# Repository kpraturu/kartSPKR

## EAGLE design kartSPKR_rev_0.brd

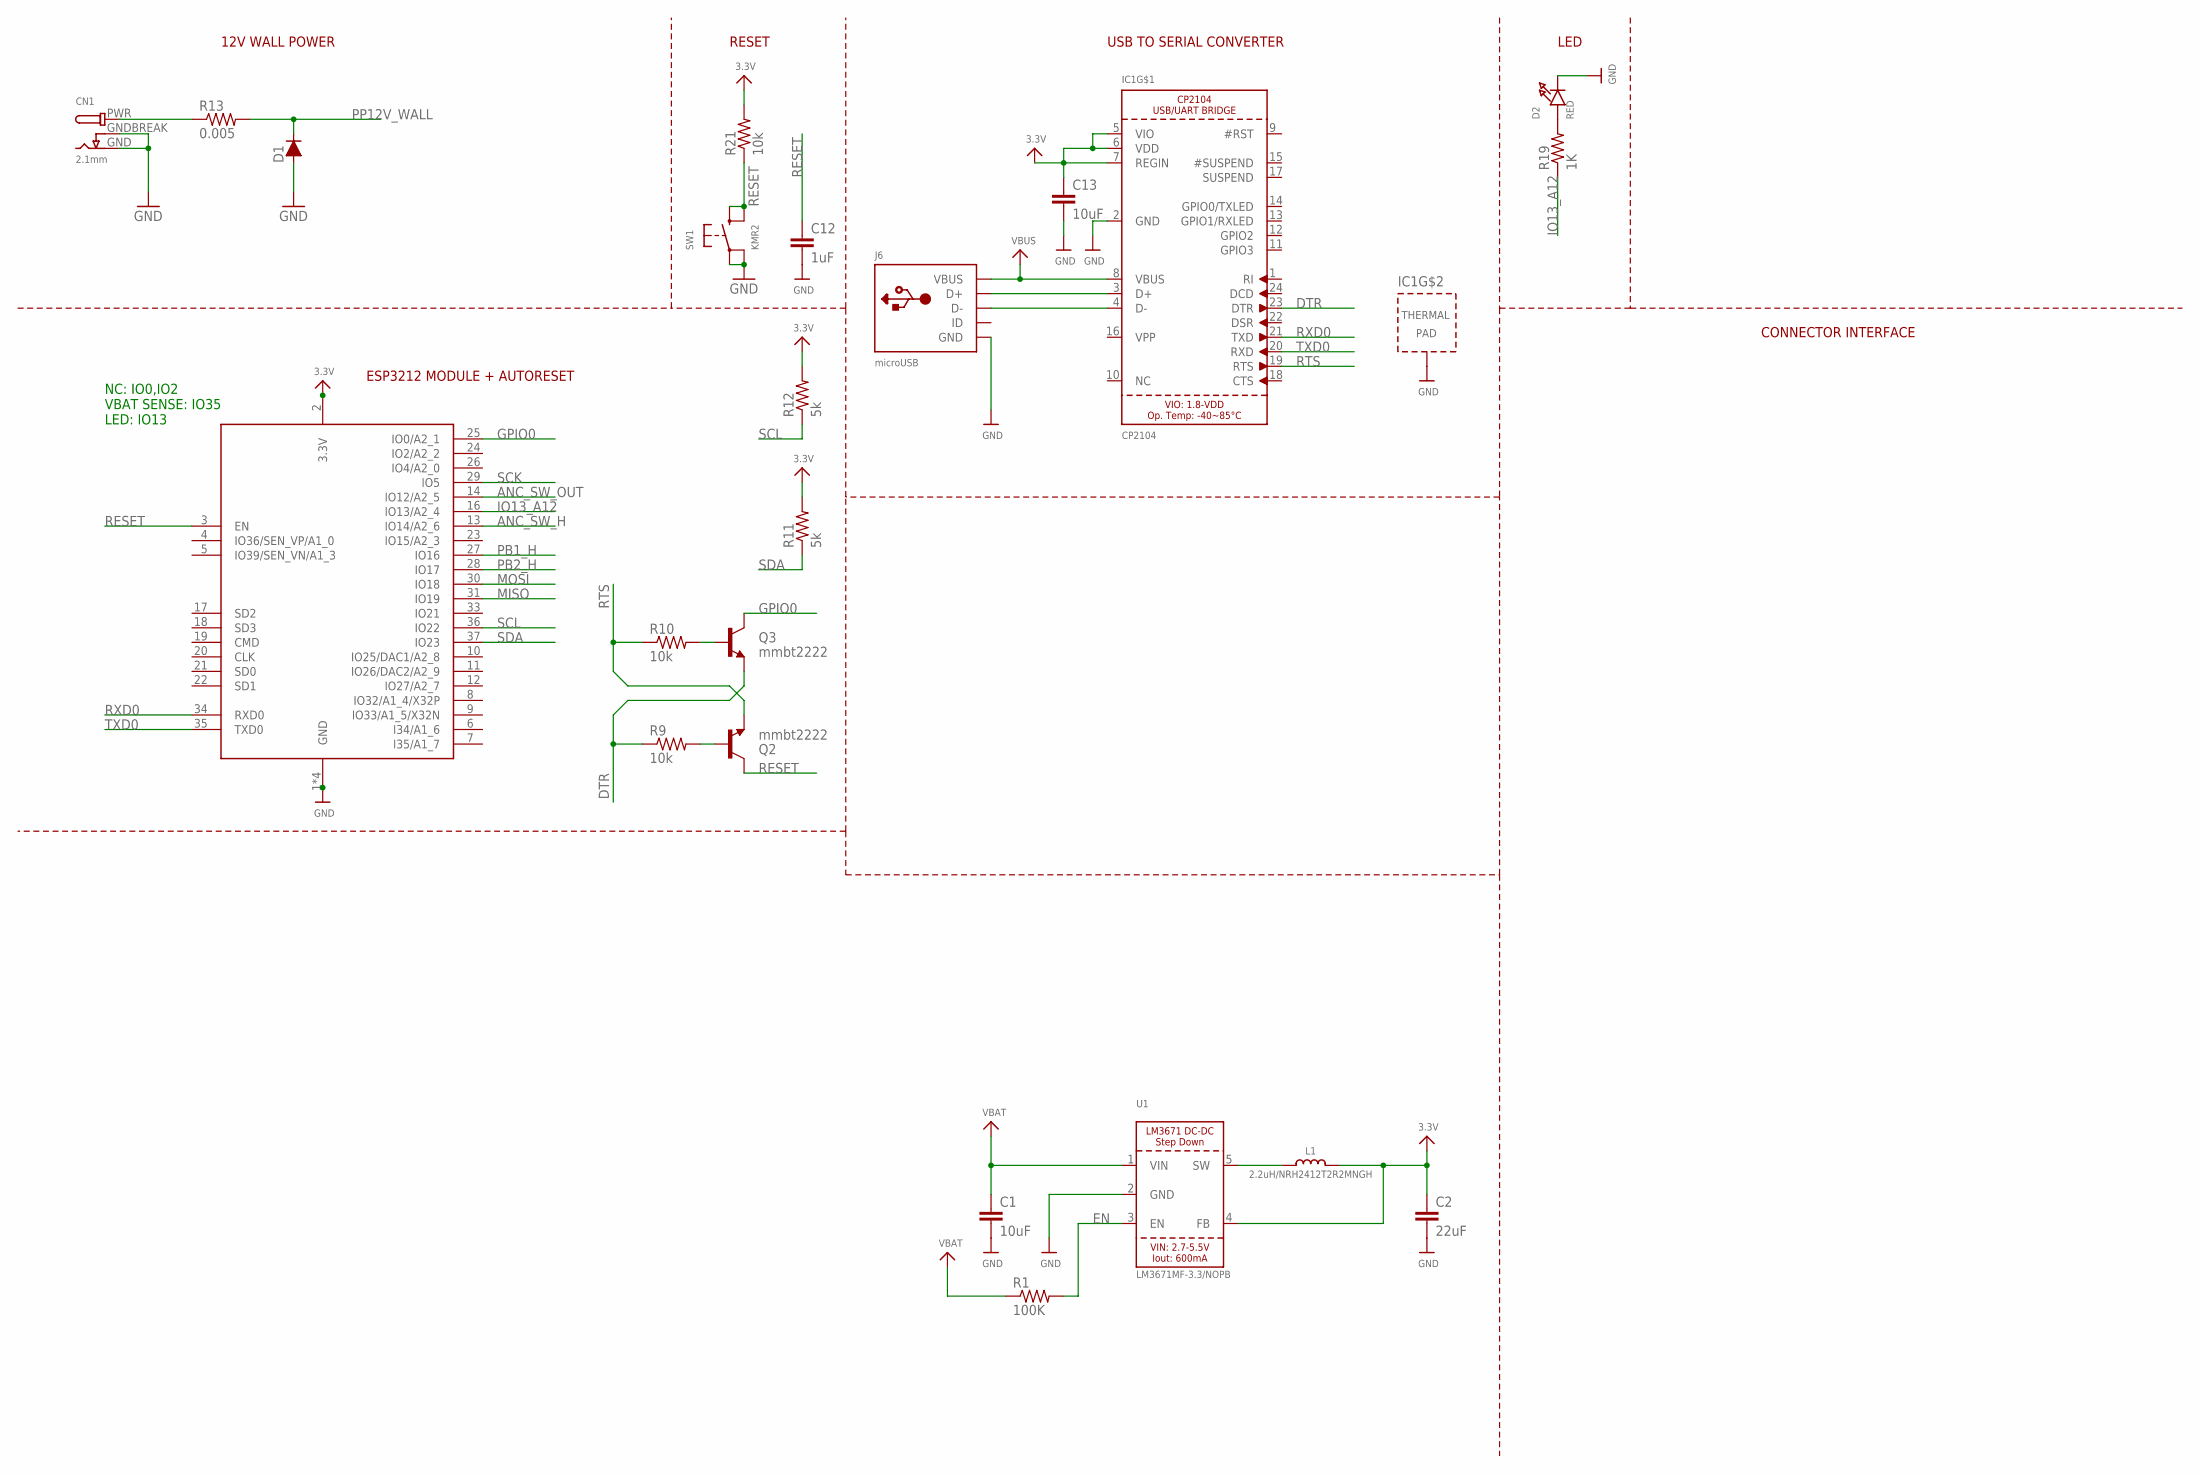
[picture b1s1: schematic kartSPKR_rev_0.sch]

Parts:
C1, C13: 10uF; C0603
C2: 22uF; C0603
C12: 1uF; C0603
CN1: 2.1mm; DCJACK_2MM_SMT
D1: D-FILL-SMB; SMB
D2: RED; CHIPLED_0805_NOOUTLINE
IC1: CP2104; QFN24_4MM_SMSC
J6: microUSB; 4UCONN_20329
L1: 2.2uH/NRH2412T2R2MNGH; INDUCTOR_TAIYOYUDEN_NRH2412T
Q2, Q3: mmbt2222; SOT23-3
R1: 100K; R0603
R9, R10, R21: 10k; R0603
R11, R12: 5k; R0603
R13: 0.005; R1206
R19: 1K; R0603
SW1: KMR2; BTN_KMR2_4.6X2.8
U1: LM3671MF-3.3/NOPB; SOT23-5
X1: ESP32_WROOM32_SKINNY; WROOM32_SKINNY

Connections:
3.3V: C2.1, C13.1, IC1.5 (VIO), IC1.6 (VDD), IC1.7 (REGIN), L1.2, R11.2, R12.2, R21.2, U1.4 (FB), X1.2 (3.3V)
ANC_SW_H: X1.13 (IO14/A2_6)
ANC_SW_OUT: X1.14 (IO12/A2_5)
DTR: IC1.23 (DTR), Q3.2 (E), R9.1
EN: R1.2, U1.3 (EN)
GND: C1.2, C2.2, C12.2, C13.2, CN1.GND, CN1.GNDBREAK, D1.2 (A), D2.C, IC1.2 (GND), IC1.THERM (TP), J6.BASE@1 (GND), J6.BASE@2 (GND), J6.GND, J6.SPRT@1 (GND), J6.SPRT@2 (GND), J6.SPRT@3 (GND), J6.SPRT@4 (GND), SW1.A, SW1.A' (P1), U1.2 (GND), X1.1 (GND), X1.15 (GND), X1.38 (GND), X1.P$1 (GND)
GPIO0: Q3.3 (C), X1.25 (IO0/A2_1)
IO13_A12: R19.1, X1.16 (IO13/A2_4)
MISO: X1.31 (IO19)
MOSI: X1.30 (IO18)
unnamed: CN1.PWR, R13.1
unnamed: IC1.3 (D+), J6.D+
unnamed: D2.A, R19.2
unnamed: IC1.4 (D-), J6.D-
unnamed: Q2.1 (B), R9.2
unnamed: Q3.1 (B), R10.2
unnamed: L1.1, U1.5 (SW)
PB1_H: X1.27 (IO16)
PB2_H: X1.28 (IO17)
PP12V_WALL: D1.1 (C), R13.2
RESET: C12.1, Q2.3 (C), R21.1, SW1.B (S), SW1.B' (S1), X1.3 (EN)
RTS: IC1.19 (RTS), Q2.2 (E), R10.1
RXD0: IC1.21 (TXD), X1.34 (RXD0)
SCK: X1.29 (IO5)
SCL: R12.1, X1.36 (IO22)
SDA: R11.1, X1.37 (IO23)
TXD0: IC1.20 (RXD), X1.35 (TXD0)
VBAT: C1.1, R1.1, U1.1 (VIN)
VBUS: IC1.8 (VBUS), J6.VBUS

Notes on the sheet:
RESET
USB TO SERIAL CONVERTER
LED
ESP3212 MODULE + AUTORESET
NC: IO0,IO2 VBAT SENSE: IO35 LED: IO13
12V WALL POWER
CONNECTOR INTERFACE

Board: 2 copper layers, 23 parts (0 on the bottom side), 22 nets, no tracks yet.

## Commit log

2019-08-31 First commit. Copied common components over.
2019-10-27 Added barrel jack and cleaned up schematic

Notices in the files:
parts and their libraries:
microbuilder: This work is placed in the public domain, and may be freely used for commercial and non-commercial work with the following conditions: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
SparkFun: Licensing: CC v3.0 Share-Alike You are welcome to use this library for commercial purposes.
